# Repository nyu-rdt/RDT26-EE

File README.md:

# RDT26-EE
NYU Robotic Design Team Electrical Engineering subsystem repo

For help with C/C++ or using git and github, refer to training presentations in the NYU RDT 2025 - 2026 / Electrical Engineering / EE Trainings google drive

## CI Status

- `platformio-main.yml` compiles `platformio_projects/RDT_2025_26_TEENSY4_1`
- `platformio-i2c-parent.yml` compiles `general_testing/ALL_i2c_can/i2c_parent_CAN`

Both workflows run on push/pull request when those folders change, and can also be run manually from the Actions tab.

## where is the robot code?

Embedded code for robot control is / will be in [/platformio_projects](./platformio_projects). code from last years robot is in [/platformio_archive](./platformio_archive) (useful to review!) check readmes to identify the right project to use.

Review docs in [/docs](./docs) for coding style, testing, and contributing guidelines.

## where are the PCBs?

all PCBs, schematics etc. are in the Google Drive or in [/HARDWARE](./HARDWARE) folder

## new files
pls try and keep new files organized in the right folders - e.g. tests in /tests, docs in /docs, hardware files in /HARDWARE etc.

when testing things try and use the platformio test framework instead of making throwaway files.

If you do need to make such files (really want to use arduino IDE or something) please place them in [/general_testing](./general_testing) so they don't clutter the main repo.

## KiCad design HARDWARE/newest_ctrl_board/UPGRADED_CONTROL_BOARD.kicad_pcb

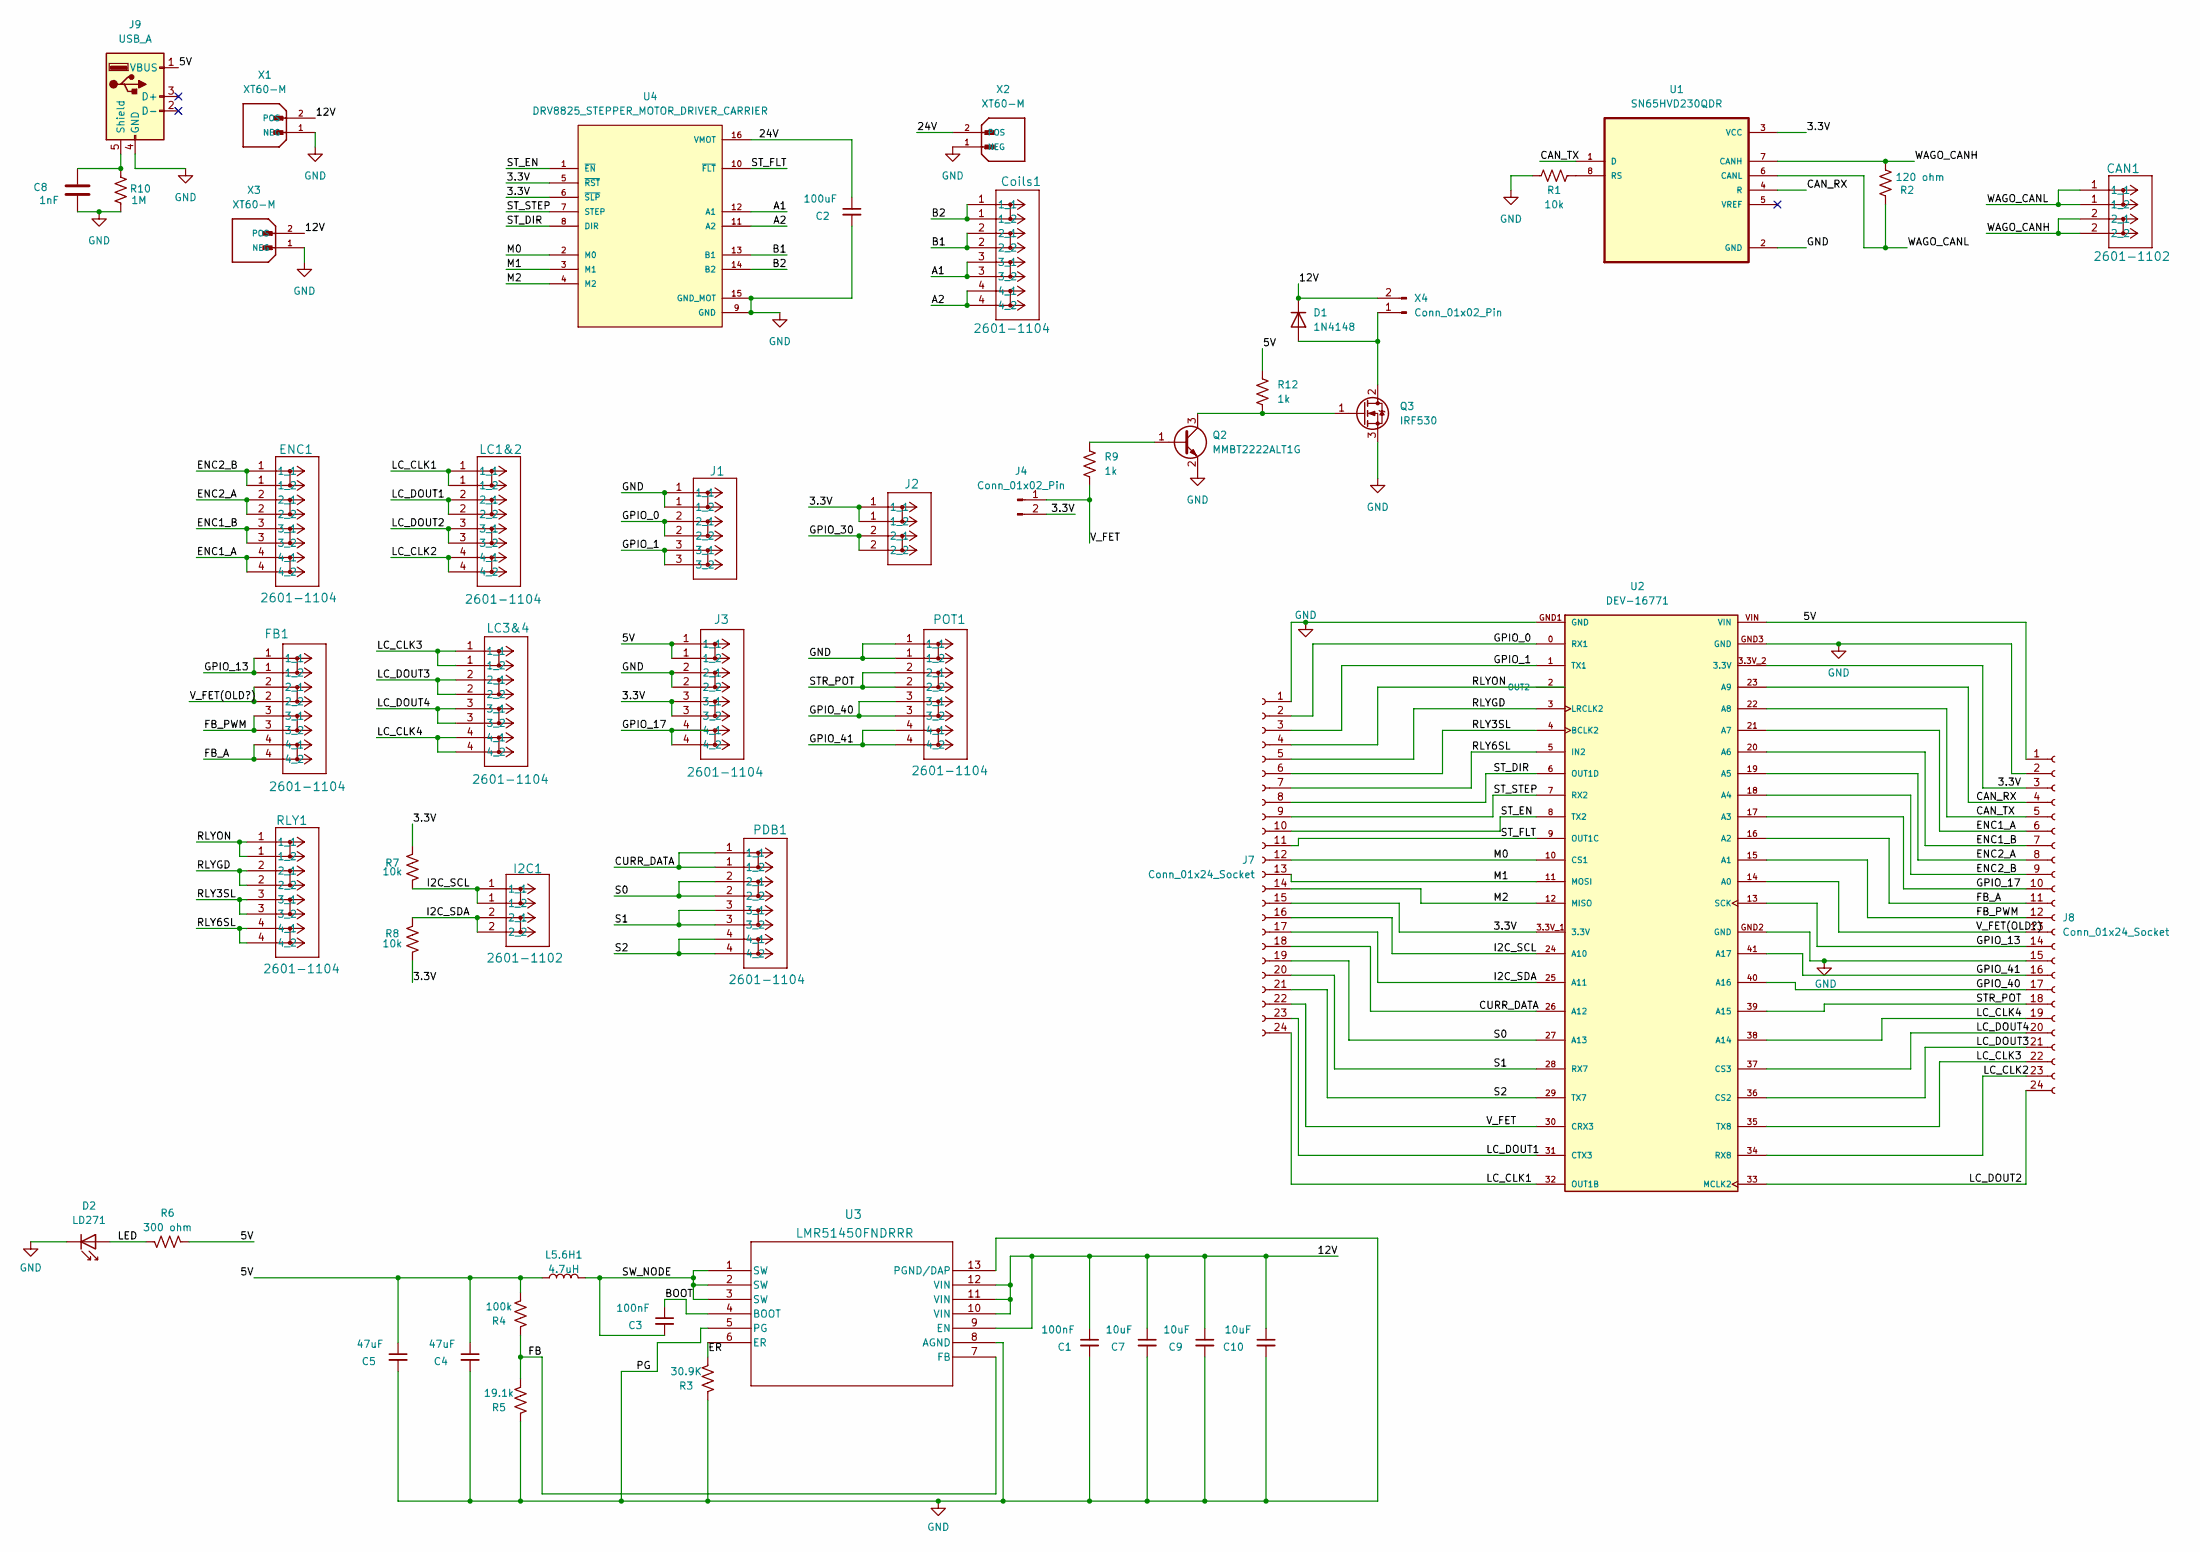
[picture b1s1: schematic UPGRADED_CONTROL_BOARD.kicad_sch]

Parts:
C1, C3: 100nF; C_0402_1005Metric_Pad0.74x0.62mm_HandSolder
C2: 100uF; C_Radial_D6.3mm_H5.0mm_P2.50mm
C4, C5: 47uF; C_1210_3225Metric_Pad1.33x2.70mm_HandSolder
C7, C9, C10: 10uF; C_0805_2012Metric_Pad1.18x1.45mm_HandSolder
C8: 1nF; C_0805_2012Metric_Pad1.18x1.45mm_HandSolder
CAN1: 2601-1102; CONN2_2601-1102_WAG
Coils1: 2601-1104; CONN4_2601-1104_WAG
D1: 1N4148; D_DO-35_SOD27_P7.62mm_Horizontal
D2: LD271; LED_D5.0mm
ENC1: 2601-1104; CONN4_2601-1104_WAG
FB1: 2601-1104; CONN4_2601-1104_WAG
I2C1: 2601-1102; CONN2_2601-1102_WAG
J1: 2604-1103; CONN3_2601-1103_WAG
J2: 236-402/334-604; CONN2_2601-1102_WAG
J3: 2601-1104; CONN4_2601-1104_WAG
J4: Conn_01x02_Pin; PinHeader_1x02_P2.54mm_Vertical
J7, J8: Conn_01x24_Socket; PinHeader_1x24_P2.54mm_Vertical
J9: USB_A; USB_A_TE_292303-4
L5.6H1: 4.7uH; L_Coilcraft_XAL6060-XXX
LC1&2, LC3&4: 2601-1104; CONN4_2601-1104_WAG
PDB1: 2601-1104; CONN4_2601-1104_WAG
POT1: 2601-1104; CONN4_2601-1104_WAG
Q2: MMBT2222ALT1G; SOT-23
Q3: IRF530; TO-220-3_Vertical
R1, R7, R8: 10k; R_0805_2012Metric
R2: 120 ohm; R_0805_2012Metric
R3: 30.9K; R_0805_2012Metric
R4: 100k; R_0805_2012Metric
R5: 19.1k; R_0805_2012Metric
R6: 300 ohm; R_0805_2012Metric
R9, R12: 1k; R_0805_2012Metric
R10: 1M; R_0805_2012Metric_Pad1.20x1.40mm_HandSolder
RLY1: 2601-1104; CONN4_2601-1104_WAG
U1: SN65HVD230QDR; SOIC127P599X175-8N
U2: DEV-16771; teensy4.1
U3: LMR51450FNDRRR; WSON_SDRRR_TEX
U4: DRV8825_STEPPER_MOTOR_DRIVER_CARRIER; IC_DRV8825_STEPPER_MOTOR_DRIVER_CARRIER
X1, X2, X3: XT60-M; AMASS_XT60-M; PARTREV V1.2
X4: Conn_01x02_Pin; AMASS_XT60-M

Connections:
/3.3V: J2.1 (1_1), J3.3 (3_1), J4.2, J7.15, J8.3, R7.2, R8.2, U1.3 (VCC), U2.3.3V_1 (3.3V), U2.3.3V_2 (3.3V), U4.5 (~RST), U4.6 (~SLP)
/5V: C4.1, C5.1, J3.1 (1_1), J8.1, J9.1 (VBUS), L5.6H1.2, R4.2, R6.2, R12.1, U2.VIN
/12V: C1.1, C7.1, C9.1, C10.1, D1.1 (K), U3.9 (EN), U3.10 (VIN), U3.11 (VIN), U3.12 (VIN), X1.2 (POS), X3.2 (POS), X4.2
/24V: C2.1, U4.16 (VMOT), X2.2 (POS)
/A1: Coils1.3 (3_1), U4.12 (A1)
/A2: Coils1.4 (4_1), U4.11 (A2)
/B1: Coils1.2 (2_1), U4.13 (B1)
/B2: Coils1.1 (1_1), U4.14 (B2)
/BOOT: C3.1, U3.4 (BOOT)
/CAN_RX: J8.4, U1.4 (R), U2.23 (A9)
/CAN_TX: J8.5, U1.1 (D), U2.22 (A8)
/CURR_DATA: J7.18, PDB1.1 (1_1), U2.26 (A12)
/ENC1_A: ENC1.4 (4_1), J8.6, U2.21 (A7)
/ENC1_B: ENC1.3 (3_1), J8.7, U2.20 (A6)
/ENC2_A: ENC1.2 (2_1), J8.8, U2.19 (A5)
/ENC2_B: ENC1.1 (1_1), J8.9, U2.18 (A4)
/ER: R3.2, U3.6 (ER)
/FB: R4.1, R5.2, U3.7 (FB)
/FB_A: FB1.4 (4_1), J8.11, U2.16 (A2)
/FB_PWM: FB1.3 (3_1), J8.12, U2.15 (A1)
/GPIO_0: J1.2 (2_1), J7.2, U2.0 (RX1)
/GPIO_1: J1.3 (3_1), J7.3, U2.1 (TX1)
/GPIO_13: FB1.1 (1_1), J8.14, U2.13 (SCK)
/GPIO_17: J3.4 (4_1), J8.10, U2.17 (A3)
/GPIO_30: J2.2 (2_1)
/GPIO_40: J8.17, POT1.3 (3_1), U2.40 (A16)
/GPIO_41: J8.16, POT1.4 (4_1), U2.41 (A17)
/I2C_SCL: I2C1.1 (1_1), J7.16, R7.1, U2.24 (A10)
/I2C_SDA: I2C1.2 (2_1), J7.17, R8.1, U2.25 (A11)
/LC_CLK1: J7.24, LC1&2.1 (1_1), U2.32 (OUT1B)
/LC_CLK2: J8.23, LC1&2.4 (4_1), U2.34 (RX8)
/LC_CLK3: J8.22, LC3&4.1 (1_1), U2.35 (TX8)
/LC_CLK4: J8.19, LC3&4.4 (4_1), U2.38 (A14)
/LC_DOUT1: J7.23, LC1&2.2 (2_1), U2.31 (CTX3)
/LC_DOUT2: J8.24, LC1&2.3 (3_1), U2.33 (MCLK2)
/LC_DOUT3: J8.21, LC3&4.2 (2_1), U2.36 (CS2)
/LC_DOUT4: J8.20, LC3&4.3 (3_1), U2.37 (CS3)
/LED: D2.2 (A), R6.1
/M0: J7.12, U2.10 (CS1), U4.2 (M0)
/M1: J7.13, U2.11 (MOSI), U4.3 (M1)
/M2: J7.14, U2.12 (MISO), U4.4 (M2)
/RLY3SL: J7.6, RLY1.3 (3_1), U2.4 (BCLK2)
/RLY6SL: J7.7, RLY1.4 (4_1), U2.5 (IN2)
/RLYGD: J7.5, RLY1.2 (2_1), U2.3 (LRCLK2)
/RLYON: J7.4, RLY1.1 (1_1), U2.2 (OUT2)
/S0: J7.19, PDB1.2 (2_1), U2.27 (A13)
/S1: J7.20, PDB1.3 (3_1), U2.28 (RX7)
/S2: J7.21, PDB1.4 (4_1), U2.29 (TX7)
/STR_POT: J8.18, POT1.2 (2_1), U2.39 (A15)
/ST_DIR: J7.8, U2.6 (OUT1D), U4.8 (DIR)
/ST_EN: J7.10, U2.8 (TX2), U4.1 (~EN)
/ST_FLT: J7.11, U2.9 (OUT1C), U4.10 (~FLT)
/ST_STEP: J7.9, U2.7 (RX2), U4.7 (STEP)
/SW_NODE: C3.2, L5.6H1.1, U3.1 (SW), U3.2 (SW), U3.3 (SW)
/V_FET: J4.1, J7.22, R9.2, U2.30 (CRX3)
/V_FET(OLD?): FB1.2 (2_1), J8.13, U2.14 (A0)
/WAGO_CANH: CAN1.2 (2_1), R2.2, U1.7 (CANH)
/WAGO_CANL: CAN1.1 (1_1), R2.1, U1.6 (CANL)
GND: C1.2, C2.2, C4.2, C5.2, C7.2, C8.2, C9.2, C10.2, D2.1 (K), J1.1 (1_1), J3.2 (2_2), J7.1, J8.2, J8.15, J9.4 (GND), POT1.1 (1_1), Q2.2 (E), Q3.3 (S), R1.1, R3.1, R5.1, R10.2, U1.2 (GND), U2.GND1 (GND), U2.GND2 (GND), U2.GND3 (GND), U3.5 (PG), U3.8 (AGND), U3.13 (PGND/DAP), U4.9 (GND), U4.15 (GND_MOT), X1.1 (NEG), X2.1 (NEG), X3.1 (NEG)
unnamed: D1.2 (A), Q3.2 (D), X4.1
unnamed: C8.1, J9.5 (Shield), R10.1
unnamed: Q2.1 (B), R9.1
unnamed: Q2.3 (C), Q3.1 (G), R12.2
unnamed: R1.2, U1.8 (RS)

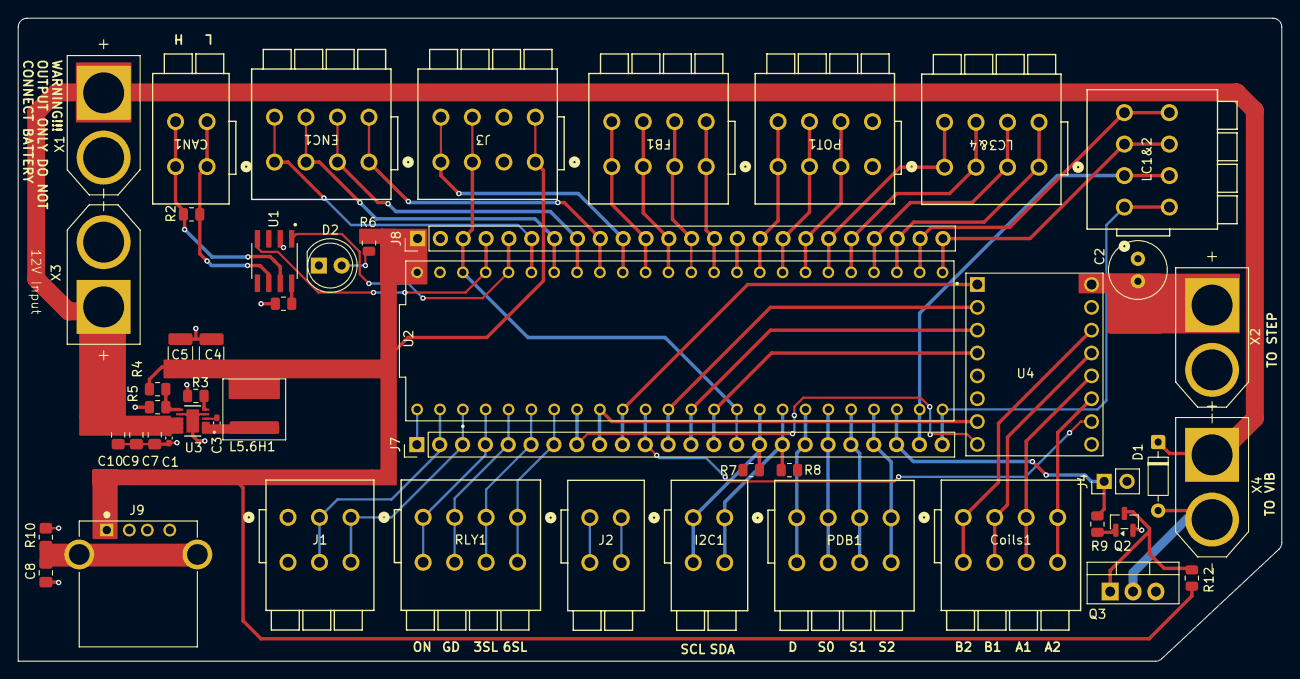
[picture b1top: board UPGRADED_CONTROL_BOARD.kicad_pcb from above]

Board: 2 copper layers, 140.5 x 71.5 mm, 50 parts (0 on the bottom side), 63 nets.

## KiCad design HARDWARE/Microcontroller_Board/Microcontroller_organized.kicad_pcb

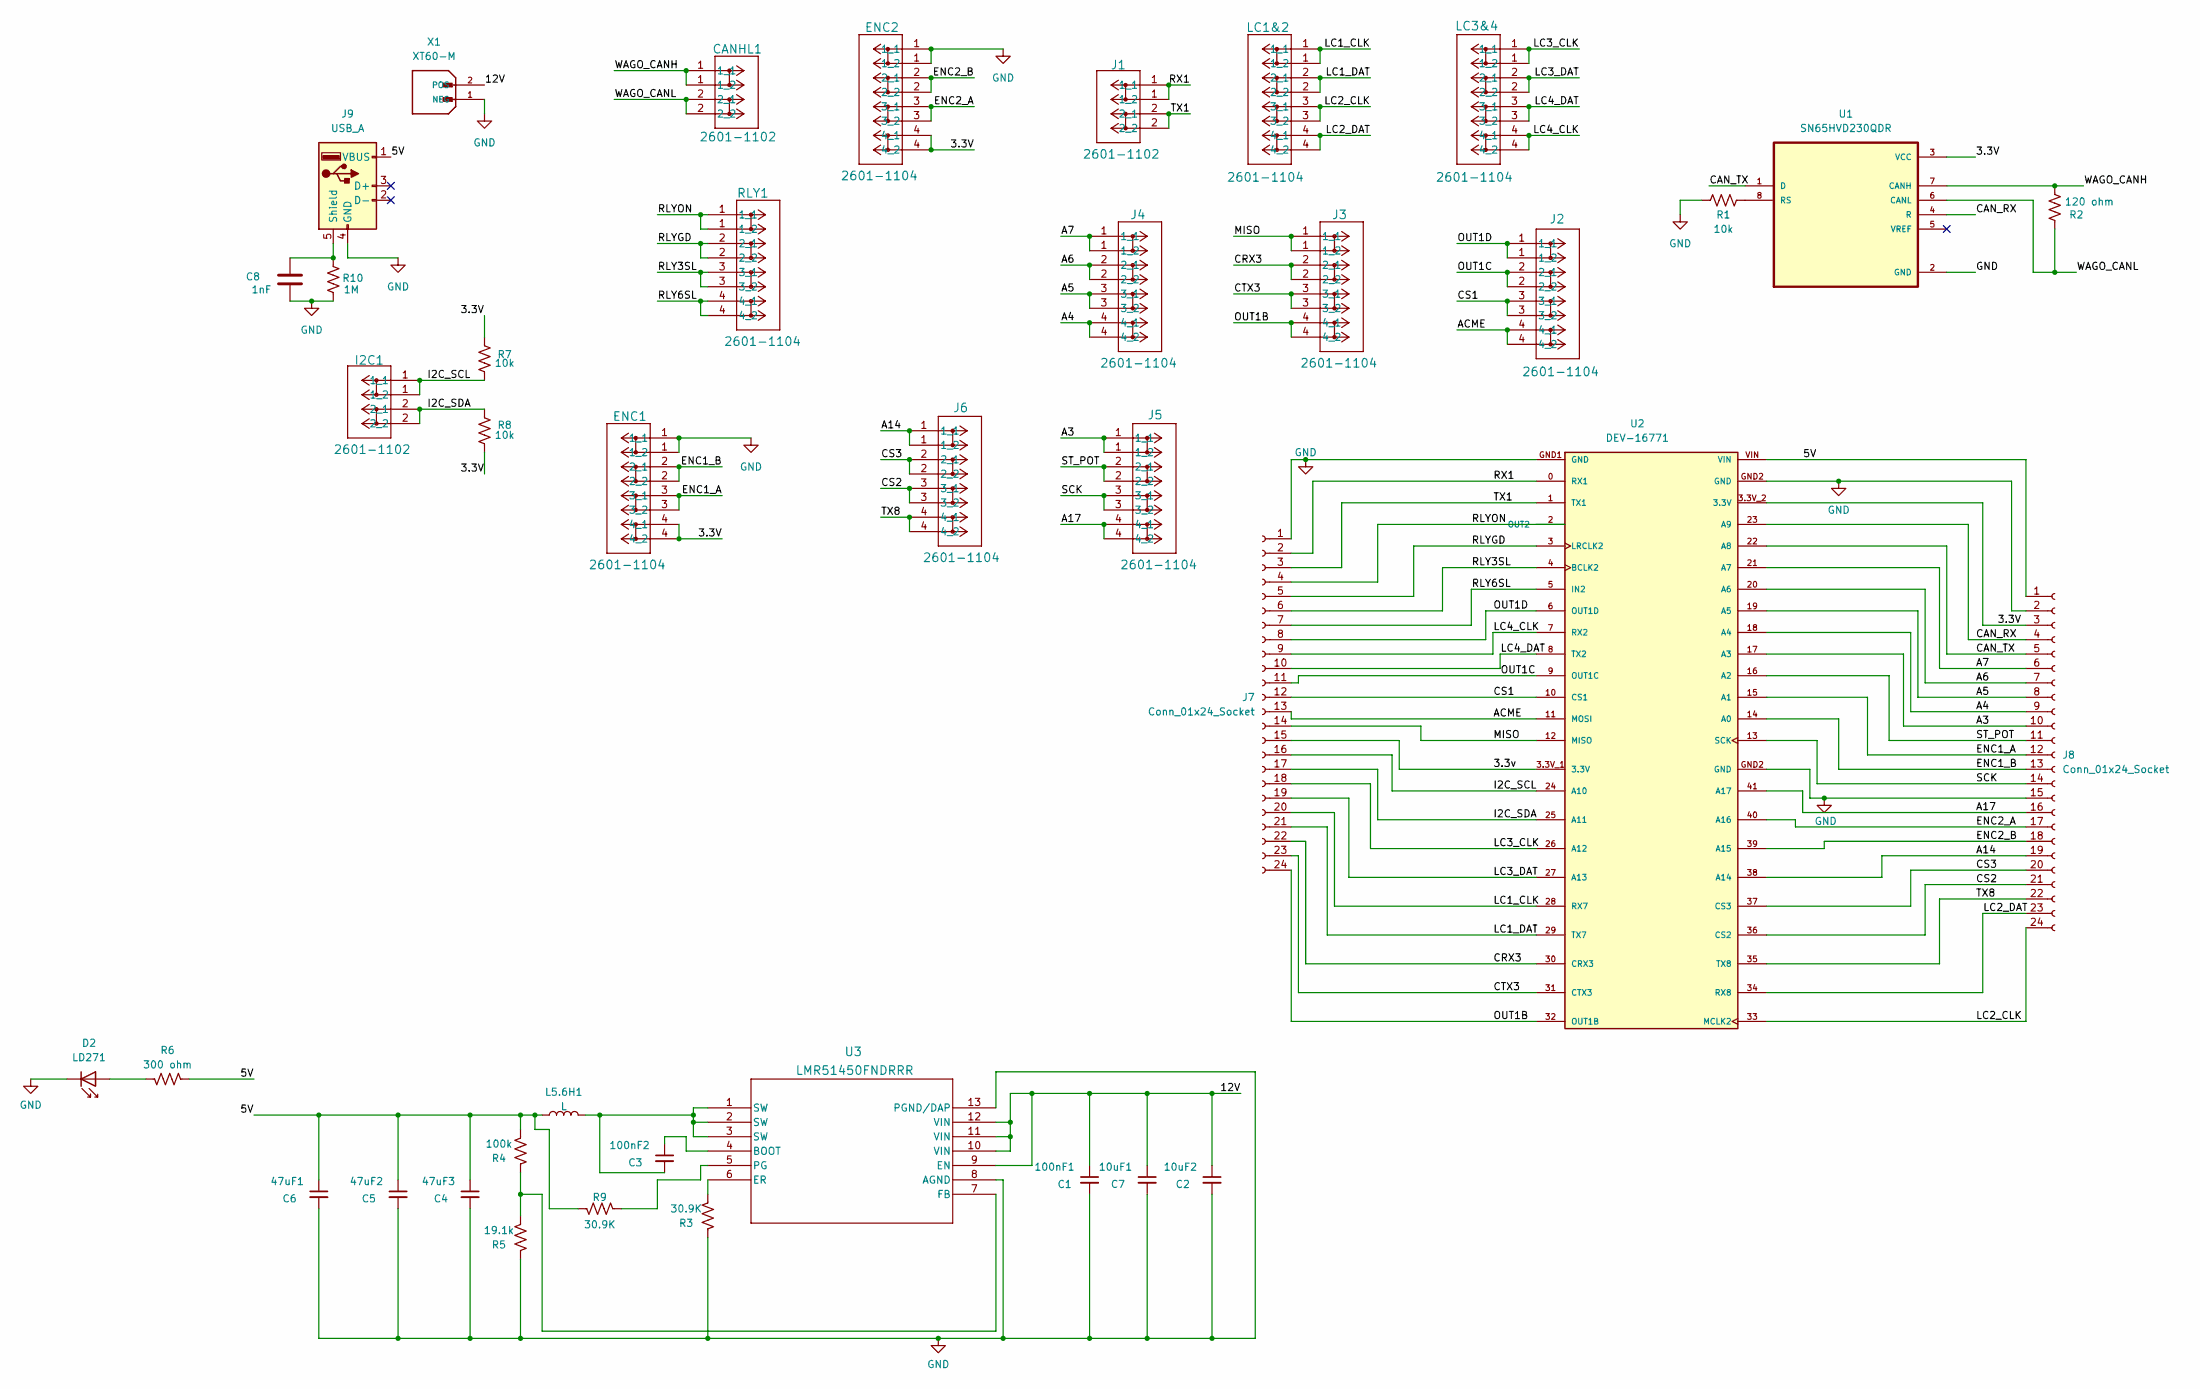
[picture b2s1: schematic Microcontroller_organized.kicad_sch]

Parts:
C1: 100nF1; C_0402_1005Metric_Pad0.74x0.62mm_HandSolder
C2: 10uF2; C_1206_3216Metric_Pad1.33x1.80mm_HandSolder
C3: 100nF2; C_0402_1005Metric_Pad0.74x0.62mm_HandSolder
C4: 47uF3; C_1210_3225Metric_Pad1.33x2.70mm_HandSolder
C5: 47uF2; C_1210_3225Metric_Pad1.33x2.70mm_HandSolder
C6: 47uF1; C_1210_3225Metric_Pad1.33x2.70mm_HandSolder
C7: 10uF1; C_1210_3225Metric_Pad1.33x2.70mm_HandSolder
C8: 1nF; C_0805_2012Metric_Pad1.18x1.45mm_HandSolder
CANHL1: 2601-1102; CONN2_2601-1102_WAG
D2: LD271; LED_D5.0mm
ENC1, ENC2: 2601-1104; CONN4_2601-1104_WAG
I2C1: 2601-1102; CONN2_2601-1102_WAG
J1: 2601-1102; CONN2_2601-1102_WAG
J2, J3, J4, J5, J6: 2601-1104; CONN4_2601-1104_WAG
J7, J8: Conn_01x24_Socket; PinHeader_1x24_P2.54mm_Vertical
J9: USB_A; USB_A_Receptacle_GCT_USB1046
L5.6H1: L; IND_IHLM-2525CZ_VIS-M
LC1&2, LC3&4: 2601-1104; CONN4_2601-1104_WAG
R1, R7, R8: 10k; R_0805_2012Metric
R2: 120 ohm; R_0805_2012Metric
R3, R9: 30.9K; R_0805_2012Metric
R4: 100k; R_0805_2012Metric
R5: 19.1k; R_0805_2012Metric
R6: 300 ohm; R_0805_2012Metric
R10: 1M; R_0805_2012Metric_Pad1.20x1.40mm_HandSolder
RLY1: 2601-1104; CONN4_2601-1104_WAG
U1: SN65HVD230QDR; SOIC127P599X175-8N
U2: DEV-16771; teensy4.1
U3: LMR51450FNDRRR; WSON_SDRRR_TEX
X1: XT60-M; AMASS_XT60-M; PARTREV V1.2

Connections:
/3.3V: ENC1.4 (4_1), ENC2.4 (4_1), J8.3, R7.2, R8.2, U1.3 (VCC), U2.3.3V_2 (3.3V)
/3.3v: J7.15, U2.3.3V_1 (3.3V)
/5V: C4.1, C5.1, C6.1, J8.1, J9.1 (VBUS), L5.6H1.2, R4.2, R6.2, R9.2, U2.VIN
/12V: C1.1, C2.1, C7.1, U3.9 (EN), U3.10 (VIN), U3.11 (VIN), U3.12 (VIN), X1.2 (POS)
/A3: J5.1 (1_1), J8.10, U2.17 (A3)
/A4: J4.4 (4_1), J8.9, U2.18 (A4)
/A5: J4.3 (3_1), J8.8, U2.19 (A5)
/A6: J4.2 (2_1), J8.7, U2.20 (A6)
/A7: J4.1 (1_1), J8.6, U2.21 (A7)
/A14: J6.1 (1_1), J8.19, U2.38 (A14)
/A17: J5.4 (4_1), J8.16, U2.41 (A17)
/ACME: J2.4 (4_1), J7.13, U2.11 (MOSI)
/CAN_RX: J8.4, U1.4 (R), U2.23 (A9)
/CAN_TX: J8.5, U1.1 (D), U2.22 (A8)
/CRX3: J3.2 (2_1), J7.22, U2.30 (CRX3)
/CS1: J2.3 (3_1), J7.12, U2.10 (CS1)
/CS2: J6.3 (3_1), J8.21, U2.36 (CS2)
/CS3: J6.2 (2_1), J8.20, U2.37 (CS3)
/CTX3: J3.3 (3_1), J7.23, U2.31 (CTX3)
/ENC1_A: ENC1.3 (3_1), J8.12, U2.15 (A1)
/ENC1_B: ENC1.2 (2_1), J8.13, U2.14 (A0)
/ENC2_A: ENC2.3 (3_1), J8.17, U2.40 (A16)
/ENC2_B: ENC2.2 (2_1), J8.18, U2.39 (A15)
/I2C_SCL: I2C1.1 (1_1), J7.16, R7.1, U2.24 (A10)
/I2C_SDA: I2C1.2 (2_1), J7.17, R8.1, U2.25 (A11)
/LC1_CLK: J7.20, LC1&2.1 (1_1), U2.28 (RX7)
/LC1_DAT: J7.21, LC1&2.2 (2_1), U2.29 (TX7)
/LC2_CLK: J8.24, LC1&2.3 (3_1), U2.33 (MCLK2)
/LC2_DAT: J8.23, LC1&2.4 (4_1), U2.34 (RX8)
/LC3_CLK: J7.18, LC3&4.1 (1_1), U2.26 (A12)
/LC3_DAT: J7.19, LC3&4.2 (2_1), U2.27 (A13)
/LC4_CLK: J7.9, LC3&4.4 (4_1), U2.7 (RX2)
/LC4_DAT: J7.10, LC3&4.3 (3_1), U2.8 (TX2)
/MISO: J3.1 (1_1), J7.14, U2.12 (MISO)
/OUT1B: J3.4 (4_1), J7.24, U2.32 (OUT1B)
/OUT1C: J2.2 (2_1), J7.11, U2.9 (OUT1C)
/OUT1D: J2.1 (1_1), J7.8, U2.6 (OUT1D)
/RLY3SL: J7.6, RLY1.3 (3_1), U2.4 (BCLK2)
/RLY6SL: J7.7, RLY1.4 (4_1), U2.5 (IN2)
/RLYGD: J7.5, RLY1.2 (2_1), U2.3 (LRCLK2)
/RLYON: J7.4, RLY1.1 (1_1), U2.2 (OUT2)
/RX1: J1.1 (1_1), J7.2, U2.0 (RX1)
/SCK: J5.3 (3_1), J8.14, U2.13 (SCK)
/ST_POT: J5.2 (2_1), J8.11, U2.16 (A2)
/TX1: J1.2 (2_1), J7.3, U2.1 (TX1)
/TX8: J6.4 (4_1), J8.22, U2.35 (TX8)
/WAGO_CANH: CANHL1.1 (1_1), R2.2, U1.7 (CANH)
/WAGO_CANL: CANHL1.2 (2_1), R2.1, U1.6 (CANL)
GND: C1.2, C2.2, C4.2, C5.2, C6.2, C7.2, C8.2, D2.1 (K), ENC1.1 (1_1), ENC2.1 (1_2), J7.1, J8.2, J8.15, J9.4 (GND), R1.1, R3.1, R5.1, R10.2, U1.2 (GND), U2.GND1 (GND), U2.GND2 (GND), U3.8 (AGND), U3.13 (PGND/DAP), X1.1 (NEG)
unnamed: C3.2, L5.6H1.1, U3.1 (SW), U3.2 (SW), U3.3 (SW)
unnamed: D2.2 (A), R6.1
unnamed: C8.1, J9.5 (Shield), R10.1
unnamed: R1.2, U1.8 (RS)
unnamed: C3.1, U3.4 (BOOT)
unnamed: R3.2, U3.6 (ER)
unnamed: R4.1, R5.2, U3.7 (FB)
unnamed: R9.1, U3.5 (PG)

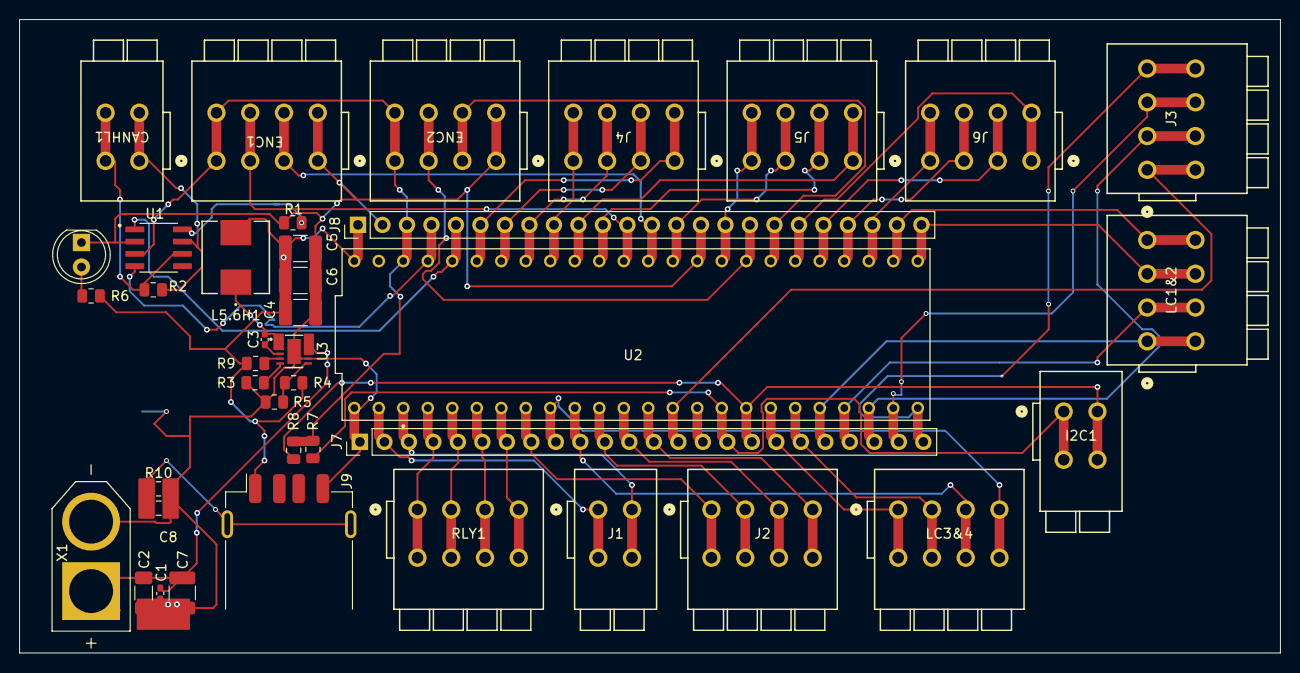
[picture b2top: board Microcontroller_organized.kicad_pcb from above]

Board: 2 copper layers, 130.7 x 65.7 mm, 40 parts (0 on the bottom side), 57 nets.

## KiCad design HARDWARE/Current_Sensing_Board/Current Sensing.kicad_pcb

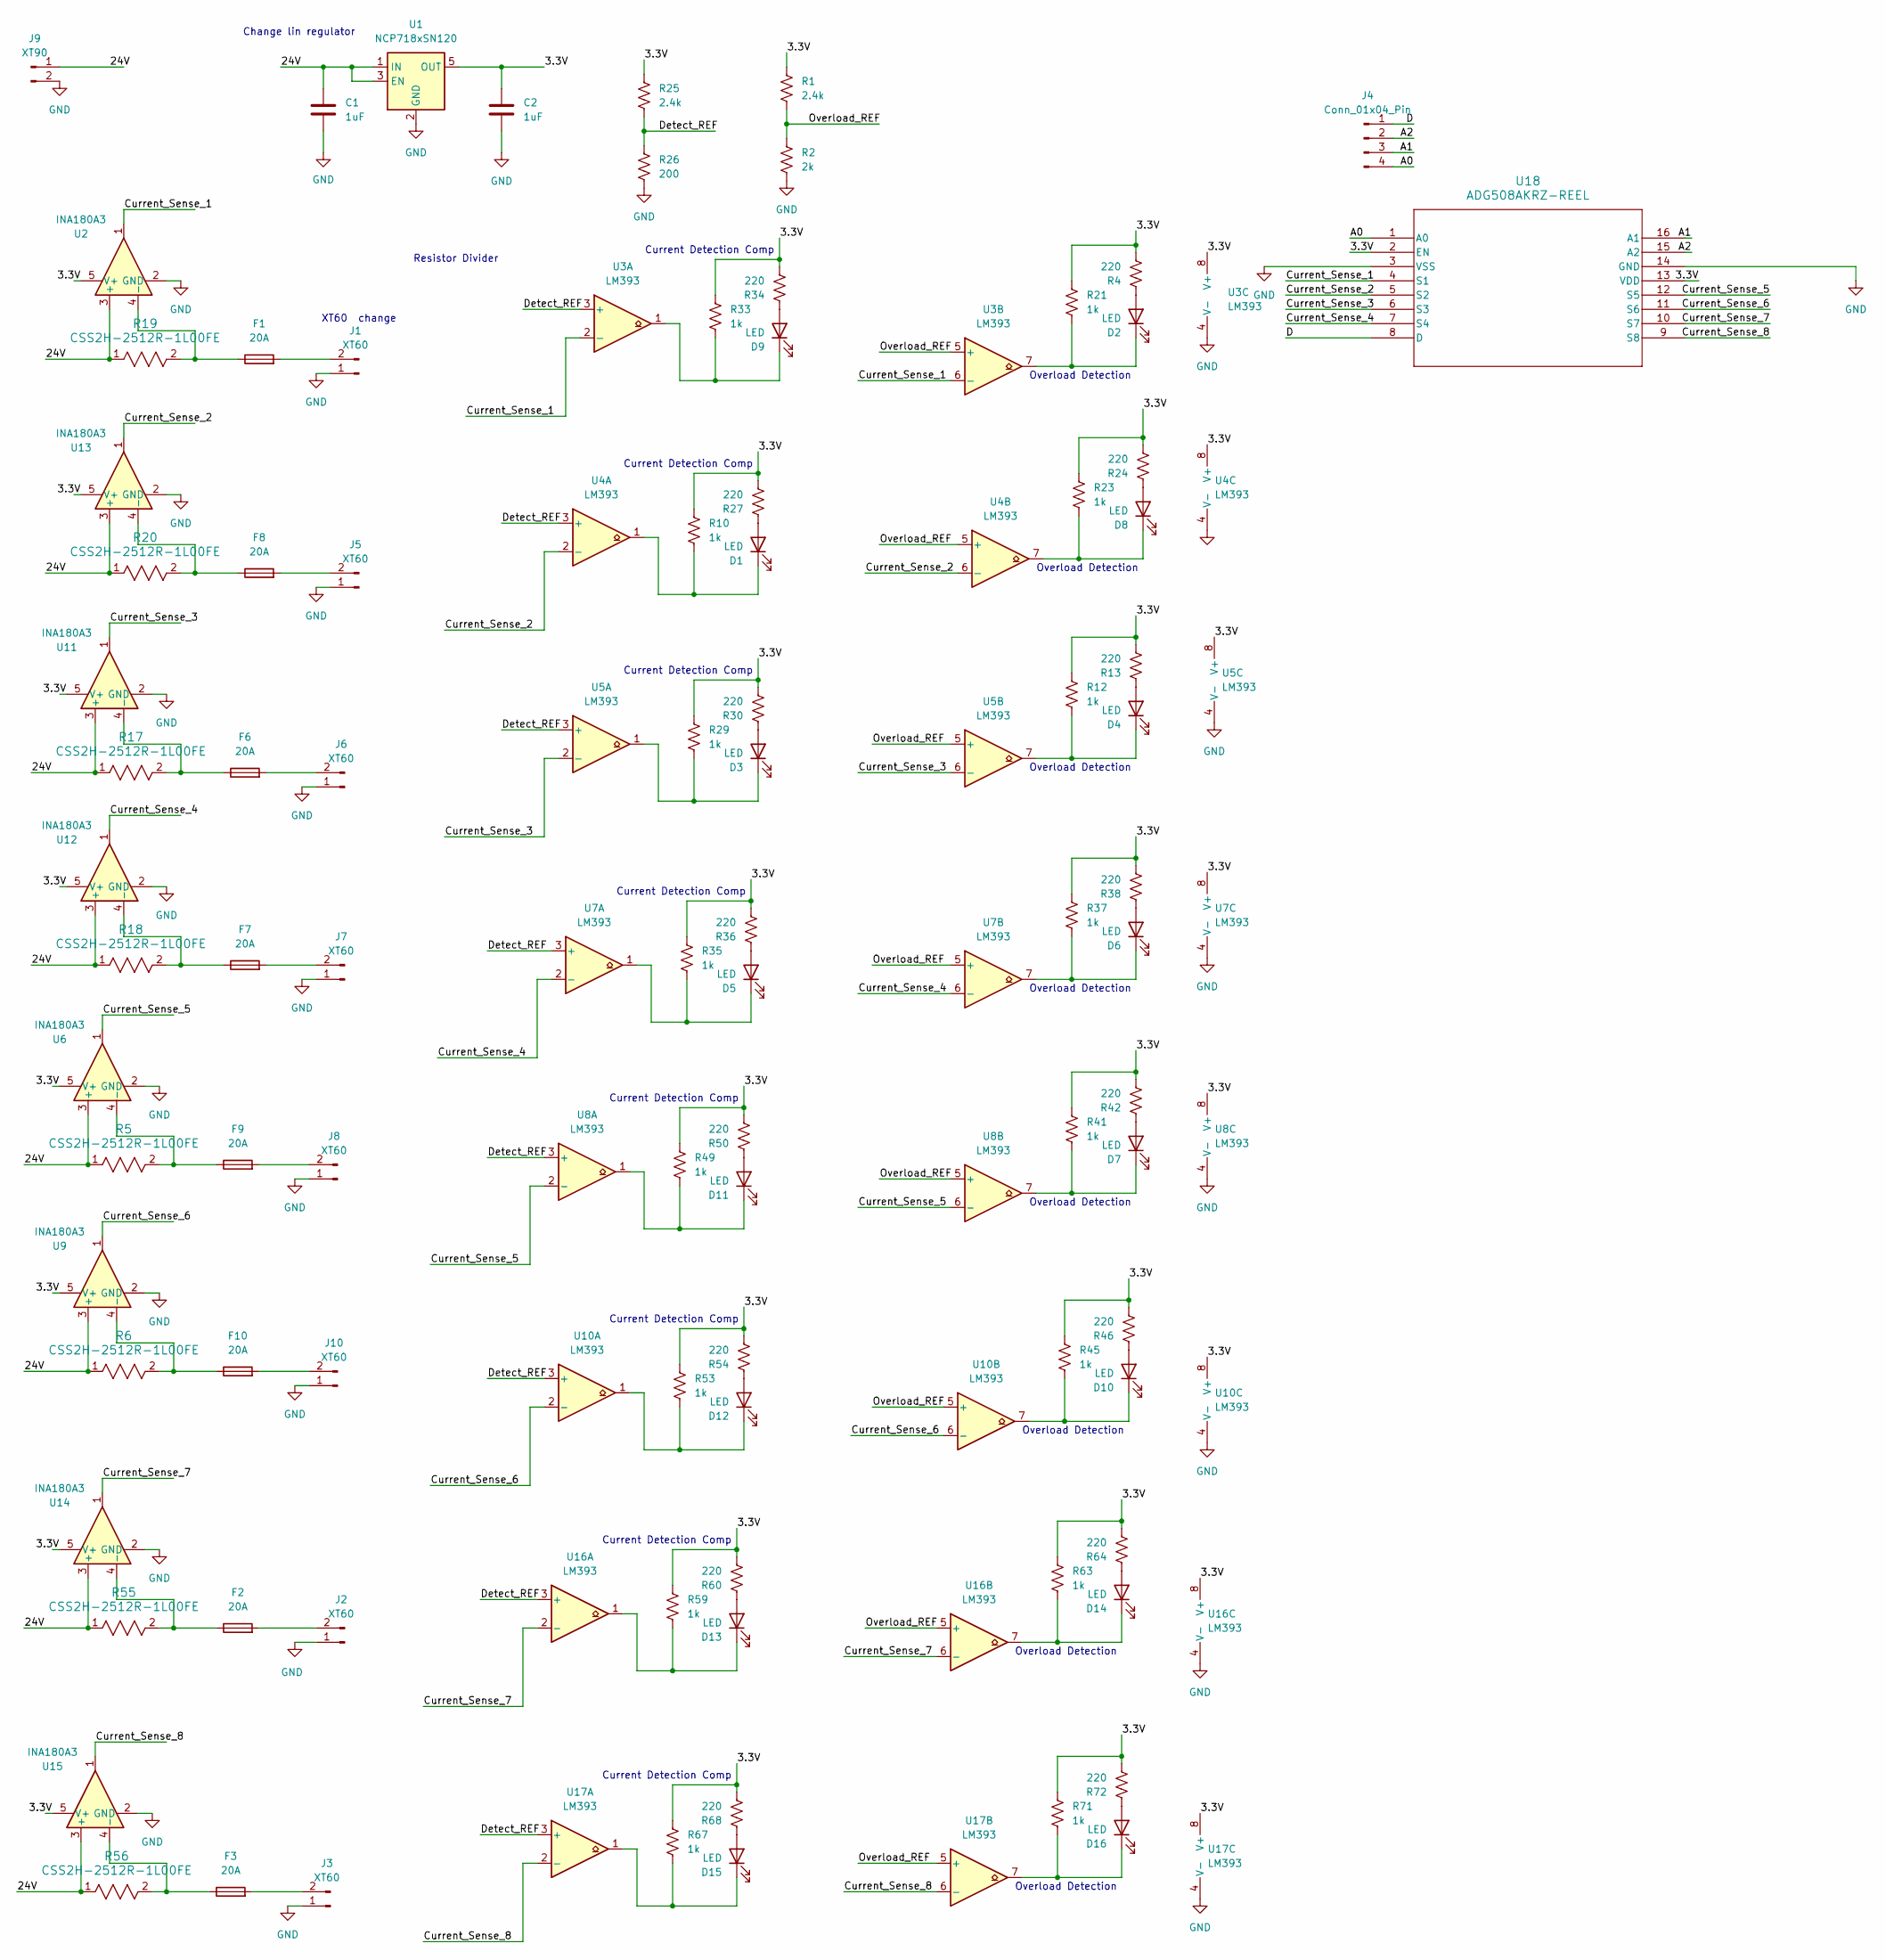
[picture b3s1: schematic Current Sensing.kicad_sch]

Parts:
C1, C2: 1uF; C_0603_1608Metric
D1, D2, D3, D4, D5, D6, D7, D8, D9, D10, D11, D12, D13, D14, D15, D16: LED; LED_D5.0mm
F1, F2, F3, F6, F7, F8, F9, F10: 20A; FUSE_3544-2
J1, J2, J3, J5, J6, J7, J8, J10: XT60; AMASS_XT60-F_1x02_P7.20mm_Vertical
J4: Conn_01x04_Pin; TerminalBlock_WAGO_2601-1104_1x04_P3.50mm_Horizontal
J9: XT90; XT90_vertical
R1, R25: 2.4k; R_0603_1608Metric
R2: 2k; R_0603_1608Metric
R4, R13, R24, R27, R30, R34, R36, R38, R42, R46, R50, R54, R60, R64, R68, R72: 220; R_0603_1608Metric
R5, R6, R17, R18, R19, R20, R55, R56: CSS2H-2512R-1L00FE; R_2512_6332Metric
R10, R12, R21, R23, R29, R33, R35, R37, R41, R45, R49, R53, R59, R63, R67, R71: 1k; R_0603_1608Metric
R26: 200; R_0603_1608Metric
U1: NCP718xSN120; SOT-23-5
U2, U6, U9, U11, U12, U13, U14, U15: INA180A3; SOT-23-5
U3, U4, U5, U7, U8, U10, U16, U17: LM393; SOIC-8_3.9x4.9mm_P1.27mm
U18: ADG508AKRZ-REEL; SOIC-16_3.9x9.9mm_P1.27mm

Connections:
/3.3V: C2.1, R1.1, R4.2, R10.1, R12.1, R13.2, R21.1, R23.1, R24.2, R25.1, R27.2, R29.1, R30.2, R33.1, R34.2, R35.1, R36.2, R37.1, R38.2, R41.1, R42.2, R45.1, R46.2, R49.1, R50.2, R53.1, R54.2, R59.1, R60.2, R63.1, R64.2, R67.1, R68.2, R71.1, R72.2, U1.5 (OUT), U2.5 (V+), U3.8 (V+), U4.8 (V+), U5.8 (V+), U6.5 (V+), U7.8 (V+), U8.8 (V+), U9.5 (V+), U10.8 (V+), U11.5 (V+), U12.5 (V+), U13.5 (V+), U14.5 (V+), U15.5 (V+), U16.8 (V+), U17.8 (V+), U18.2 (EN), U18.13 (VDD)
/24V: C1.1, J9.1, R5.1, R6.1, R17.1, R18.1, R19.1, R20.1, R55.1, R56.1, U1.1 (IN), U1.3 (EN), U2.3 (+), U6.3 (+), U9.3 (+), U11.3 (+), U12.3 (+), U13.3 (+), U14.3 (+), U15.3 (+)
/A0: J4.4, U18.1 (A0)
/A1: J4.3, U18.16 (A1)
/A2: J4.2, U18.15 (A2)
/Current_Sense_1: U2.1, U3.2 (-), U3.6 (-), U18.4 (S1)
/Current_Sense_2: U4.2 (-), U4.6 (-), U13.1, U18.5 (S2)
/Current_Sense_3: U5.2 (-), U5.6 (-), U11.1, U18.6 (S3)
/Current_Sense_4: U7.2 (-), U7.6 (-), U12.1, U18.7 (S4)
/Current_Sense_5: U6.1, U8.2 (-), U8.6 (-), U18.12 (S5)
/Current_Sense_6: U9.1, U10.2 (-), U10.6 (-), U18.11 (S6)
/Current_Sense_7: U14.1, U16.2 (-), U16.6 (-), U18.10 (S7)
/Current_Sense_8: U15.1, U17.2 (-), U17.6 (-), U18.9 (S8)
/D: J4.1, U18.8 (D)
/Detect_REF: R25.2, R26.1, U3.3 (+), U4.3 (+), U5.3 (+), U7.3 (+), U8.3 (+), U10.3 (+), U16.3 (+), U17.3 (+)
/Overload_REF: R1.2, R2.1, U3.5 (+), U4.5 (+), U5.5 (+), U7.5 (+), U8.5 (+), U10.5 (+), U16.5 (+), U17.5 (+)
GND: C1.2, C2.2, J1.1 (Pin_2), J2.1 (Pin_2), J3.1 (Pin_2), J5.1 (Pin_2), J6.1 (Pin_2), J7.1 (Pin_2), J8.1 (Pin_2), J9.2, J10.1 (Pin_2), R2.2, R26.2, U1.2 (GND), U2.2 (GND), U3.4 (V-), U4.4 (V-), U5.4 (V-), U6.2 (GND), U7.4 (V-), U8.4 (V-), U9.2 (GND), U10.4 (V-), U11.2 (GND), U12.2 (GND), U13.2 (GND), U14.2 (GND), U15.2 (GND), U16.4 (V-), U17.4 (V-), U18.3 (VSS), U18.14 (GND)
unnamed: D1.2 (A), R27.1
unnamed: D1.1 (K), R10.2, U4.1
unnamed: D2.2 (A), R4.1
unnamed: D2.1 (K), R21.2, U3.7
unnamed: D3.2 (A), R30.1
unnamed: D3.1 (K), R29.2, U5.1
unnamed: D4.2 (A), R13.1
unnamed: D4.1 (K), R12.2, U5.7
unnamed: D5.2 (A), R36.1
unnamed: D5.1 (K), R35.2, U7.1
unnamed: D6.2 (A), R38.1
unnamed: D6.1 (K), R37.2, U7.7
unnamed: D7.2 (A), R42.1
unnamed: D7.1 (K), R41.2, U8.7
unnamed: D8.2 (A), R24.1
unnamed: D8.1 (K), R23.2, U4.7
unnamed: D9.2 (A), R34.1
unnamed: D9.1 (K), R33.2, U3.1
unnamed: D10.2 (A), R46.1
unnamed: D10.1 (K), R45.2, U10.7
unnamed: D11.2 (A), R50.1
unnamed: D11.1 (K), R49.2, U8.1
unnamed: D12.2 (A), R54.1
unnamed: D12.1 (K), R53.2, U10.1
unnamed: D13.2 (A), R60.1
unnamed: D13.1 (K), R59.2, U16.1
unnamed: D14.2 (A), R64.1
unnamed: D14.1 (K), R63.2, U16.7
unnamed: D15.2 (A), R68.1
unnamed: D15.1 (K), R67.2, U17.1
unnamed: D16.2 (A), R72.1
unnamed: D16.1 (K), R71.2, U17.7
unnamed: F1.2, J1.2 (Pin_1)
unnamed: F2.2, J2.2 (Pin_1)
unnamed: F3.2, J3.2 (Pin_1)
unnamed: F8.2, J5.2 (Pin_1)
unnamed: F6.2, J6.2 (Pin_1)
unnamed: F7.2, J7.2 (Pin_1)
unnamed: F9.2, J8.2 (Pin_1)
unnamed: F10.2, J10.2 (Pin_1)
unnamed: F1.1, R19.2, U2.4 (-)
unnamed: F9.1, R5.2, U6.4 (-)
unnamed: F10.1, R6.2, U9.4 (-)
unnamed: F6.1, R17.2, U11.4 (-)
unnamed: F7.1, R18.2, U12.4 (-)
unnamed: F8.1, R20.2, U13.4 (-)
unnamed: F2.1, R55.2, U14.4 (-)
unnamed: F3.1, R56.2, U15.4 (-)

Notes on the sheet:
Overload Detection
Resistor Divider
Current Detection Comp
Change lin regulator
XT60 change

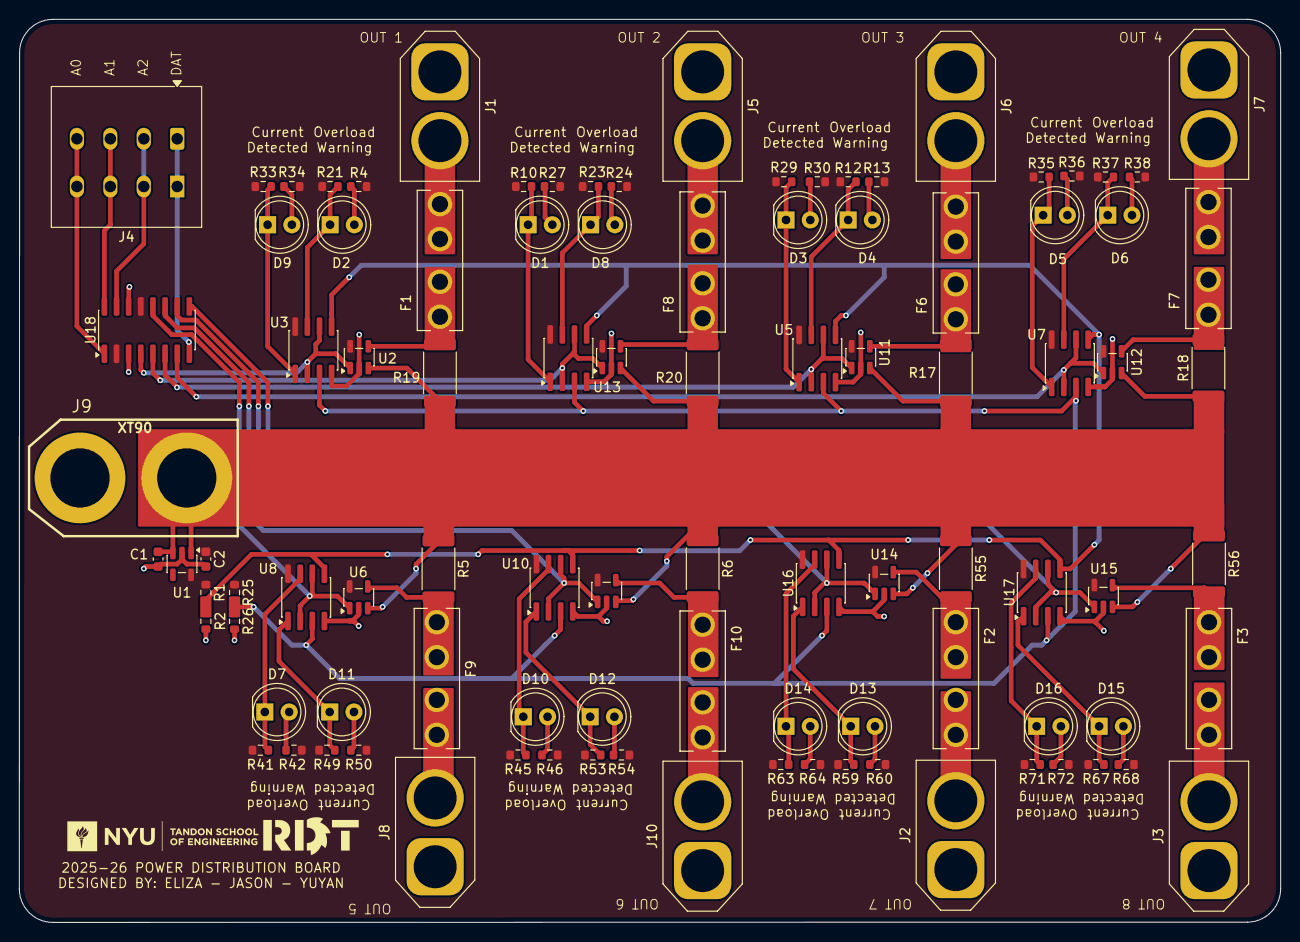
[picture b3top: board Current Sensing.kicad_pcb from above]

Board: 2 copper layers, 132.0 x 94.5 mm, 98 parts (0 on the bottom side), 65 nets.
